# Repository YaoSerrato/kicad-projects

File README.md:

# KiCad Projects
This repository contains all the source files for the KiCad projects from the Udemy course "KiCad Like a Pro" in its 2nd edition.

## Arduino clone
This project consisted on designing the schematic and PCB for an Arduino-like board.

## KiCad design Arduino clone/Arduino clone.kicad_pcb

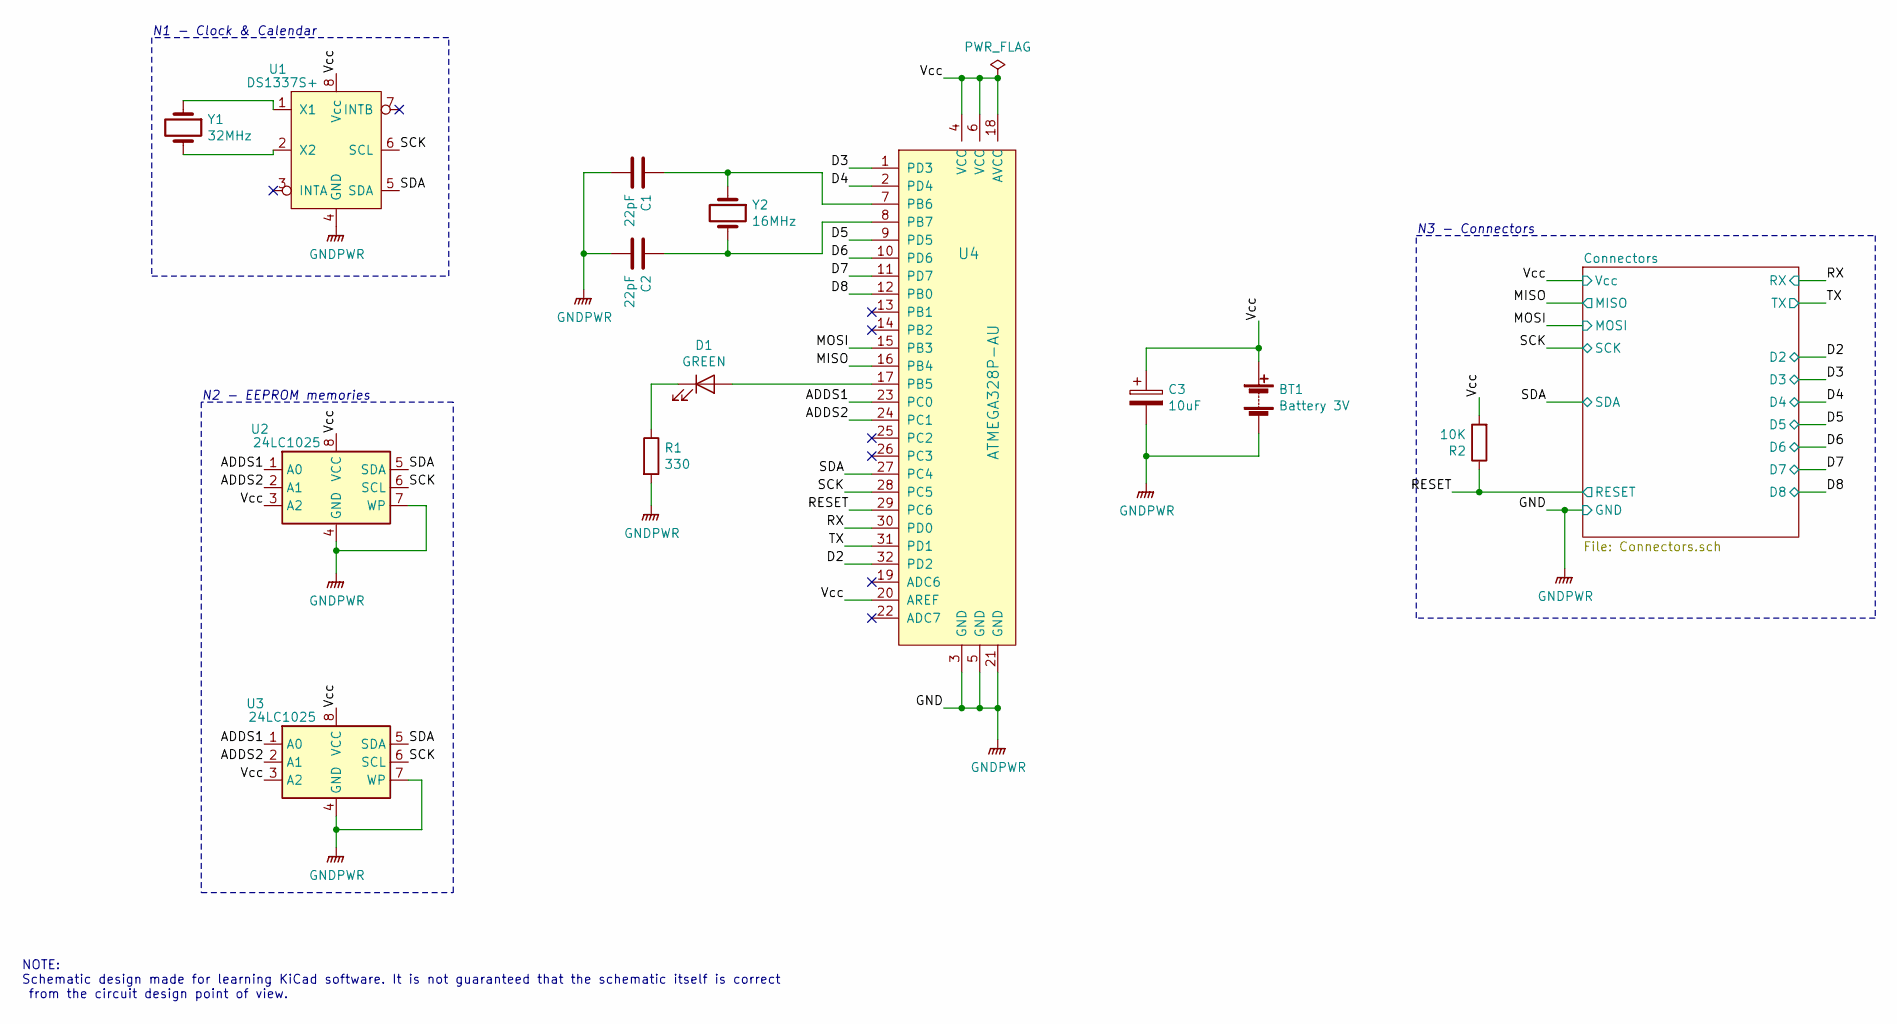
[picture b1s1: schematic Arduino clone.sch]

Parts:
BT1: Battery 3V; PinHeader_1x02_P2.54mm_Vertical
C1, C2: 22pF; C_0805_2012Metric_Pad1.15x1.40mm_HandSolder
C3: 10uF; C_0805_2012Metric_Pad1.15x1.40mm_HandSolder
D1: GREEN; LED_0805_2012Metric_Pad1.15x1.40mm_HandSolder
R1: 330; R_0805_2012Metric_Pad1.15x1.40mm_HandSolder
R2: 10K; R_0805_2012Metric_Pad1.15x1.40mm_HandSolder
U1: DS1337S+; SO-8_5.3x6.2mm_P1.27mm
U2, U3: 24LC1025; SOIJ-8_5.3x5.3mm_P1.27mm
U4: ATMEGA328P-AU; TQFP-32_7x7mm; MPN ATMEGA328P-AU; Digi-Key_PN ATMEGA328P-AU-ND
Y1: 32MHz; Crystal_SMD_MicroCrystal_CC7V-T1A-2Pin_3.2x1.5mm
Y2: 16MHz; Crystal_SMD_5032-2Pin_5.0x3.2mm_HandSoldering

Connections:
/ADDS1: U2.1 (A0), U3.1 (A0), U4.23 (PC0)
/ADDS2: U2.2 (A1), U3.2 (A1), U4.24 (PC1)
/D2: U4.32 (PD2); also elsewhere on the board
/D3: U4.1 (PD3); also elsewhere on the board
/D4: U4.2 (PD4); also elsewhere on the board
/D5: U4.9 (PD5); also elsewhere on the board
/D6: U4.10 (PD6); also elsewhere on the board
/D7: U4.11 (PD7); also elsewhere on the board
/D8: U4.12 (PB0); also elsewhere on the board
/MISO: U4.16 (PB4); also elsewhere on the board
/MOSI: U4.15 (PB3); also elsewhere on the board
/RESET: R2.1, U4.29 (PC6); also elsewhere on the board
/RX: U4.30 (PD0); also elsewhere on the board
/SCK: U1.6 (SCL), U2.6 (SCL), U3.6 (SCL), U4.28 (PC5); also elsewhere on the board
/SDA: U1.5 (SDA), U2.5 (SDA), U3.5 (SDA), U4.27 (PC4); also elsewhere on the board
/TX: U4.31 (PD1); also elsewhere on the board
/Vcc: BT1.1 (+), C3.1, R2.2, U1.8 (Vcc), U2.3 (A2), U2.8 (VCC), U3.3 (A2), U3.8 (VCC), U4.4 (VCC), U4.6 (VCC), U4.18 (AVCC), U4.20 (AREF); also elsewhere on the board
GNDPWR: BT1.2 (-), C1.2, C2.2, C3.2, R1.2, U1.4 (GND), U2.4 (GND), U2.7 (WP), U3.4 (GND), U3.7 (WP), U4.3 (GND), U4.5 (GND), U4.21 (GND); also elsewhere on the board
unnamed: C1.1, U4.7 (PB6), Y2.1
unnamed: C2.1, U4.8 (PB7), Y2.2
unnamed: D1.1 (K), R1.1
unnamed: D1.2 (A), U4.17 (PB5)
unnamed: U1.1 (X1), Y1.1
unnamed: U1.2 (X2), Y1.2

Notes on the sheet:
NOTE: Schematic design made for learning KiCad software. It is not guaranteed that the schematic itself is correct from the circuit design point of view.
N1 - Clock & Calendar
N2 - EEPROM memories
N3 - Connectors

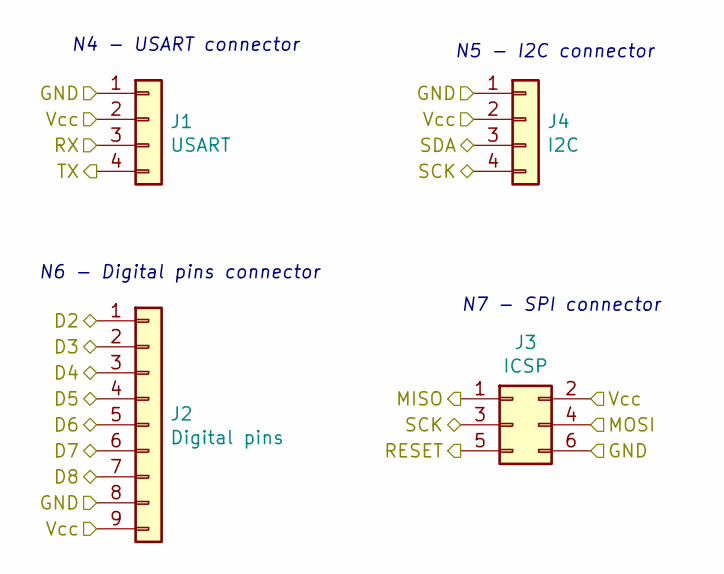
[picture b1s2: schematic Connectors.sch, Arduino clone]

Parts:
J1: USART; PinHeader_1x04_P2.54mm_Vertical
J2: Digital pins; PinHeader_1x09_P2.54mm_Vertical
J3: ICSP; PinHeader_2x03_P2.54mm_Vertical
J4: I2C; PinHeader_1x04_P2.54mm_Vertical

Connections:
/D2: J2.1; also elsewhere on the board
/D3: J2.2; also elsewhere on the board
/D4: J2.3; also elsewhere on the board
/D5: J2.4; also elsewhere on the board
/D6: J2.5; also elsewhere on the board
/D7: J2.6; also elsewhere on the board
/D8: J2.7; also elsewhere on the board
/MISO: J3.1; also elsewhere on the board
/MOSI: J3.4; also elsewhere on the board
/RESET: J3.5; also elsewhere on the board
/RX: J1.3; also elsewhere on the board
/SCK: J3.3, J4.4; also elsewhere on the board
/SDA: J4.3; also elsewhere on the board
/TX: J1.4; also elsewhere on the board
/Vcc: J1.2, J2.9, J3.2, J4.2; also elsewhere on the board
GNDPWR: J1.1, J2.8, J3.6, J4.1; also elsewhere on the board

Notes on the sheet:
N4 - USART connector
N5 - I2C connector
N6 - Digital pins connector
N7 - SPI connector

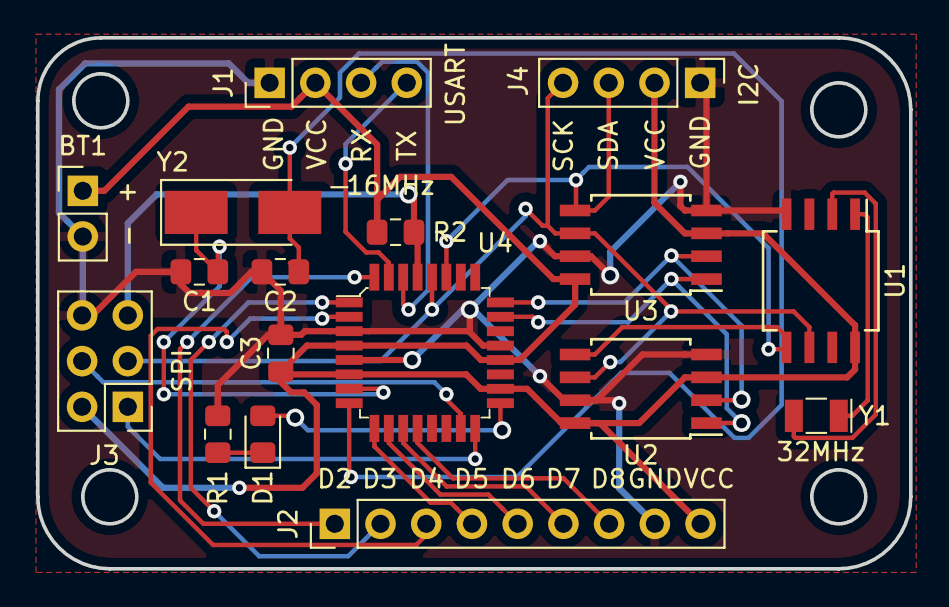
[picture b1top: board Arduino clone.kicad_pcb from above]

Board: 2 copper layers, 48.5 x 29.5 mm, 17 parts (0 on the bottom side), 24 nets.

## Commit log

2020-06-04 .gitignore
    Added .gitignore file.
2020-06-04 Arduino clone
    Added the KiCad project files.
2020-06-05 Page settings
    Added page settings: title, author, date, version, company.
2020-06-05 Symbols
    Added project symbols.
2020-06-05 Connectors file
    Added file Connectors.sch as a child schematic file.
2020-06-05 ATmega328P-AU symbol.
    Added the symbol for the ATmega328P-AU from the DigiKey KiCad library.
2020-06-06 Custom RTC symbol
    Added custom RTC symbol to schematic.
2020-06-06 Crystals
    Added missing crystals symbols.
2020-06-06 Arrange & Annotate
    Arranged and annotated symbols in schematics.
2020-06-06 Footprints & Values
    Made footprint associations and added values to symbols.
2020-06-07 Wiring
    Made the wiring of the schematic.
2020-06-07 Comments
    Added block comments.
2020-06-07 Netlist.
    Added netlist file. You should generate it on your side since .net extension is in the .gitignore file.
2020-06-07 Board setup
    Set design rules.
2020-06-07 Placing
    Finished placing of components.
2020-06-07 Routing.
    FInished routing.
2020-09-18 Updated README.md
    Added description for the Arduino clone project.
2020-09-18 Added Arduino-clone images.
2020-09-18 Added images for the Arduino clone project.
